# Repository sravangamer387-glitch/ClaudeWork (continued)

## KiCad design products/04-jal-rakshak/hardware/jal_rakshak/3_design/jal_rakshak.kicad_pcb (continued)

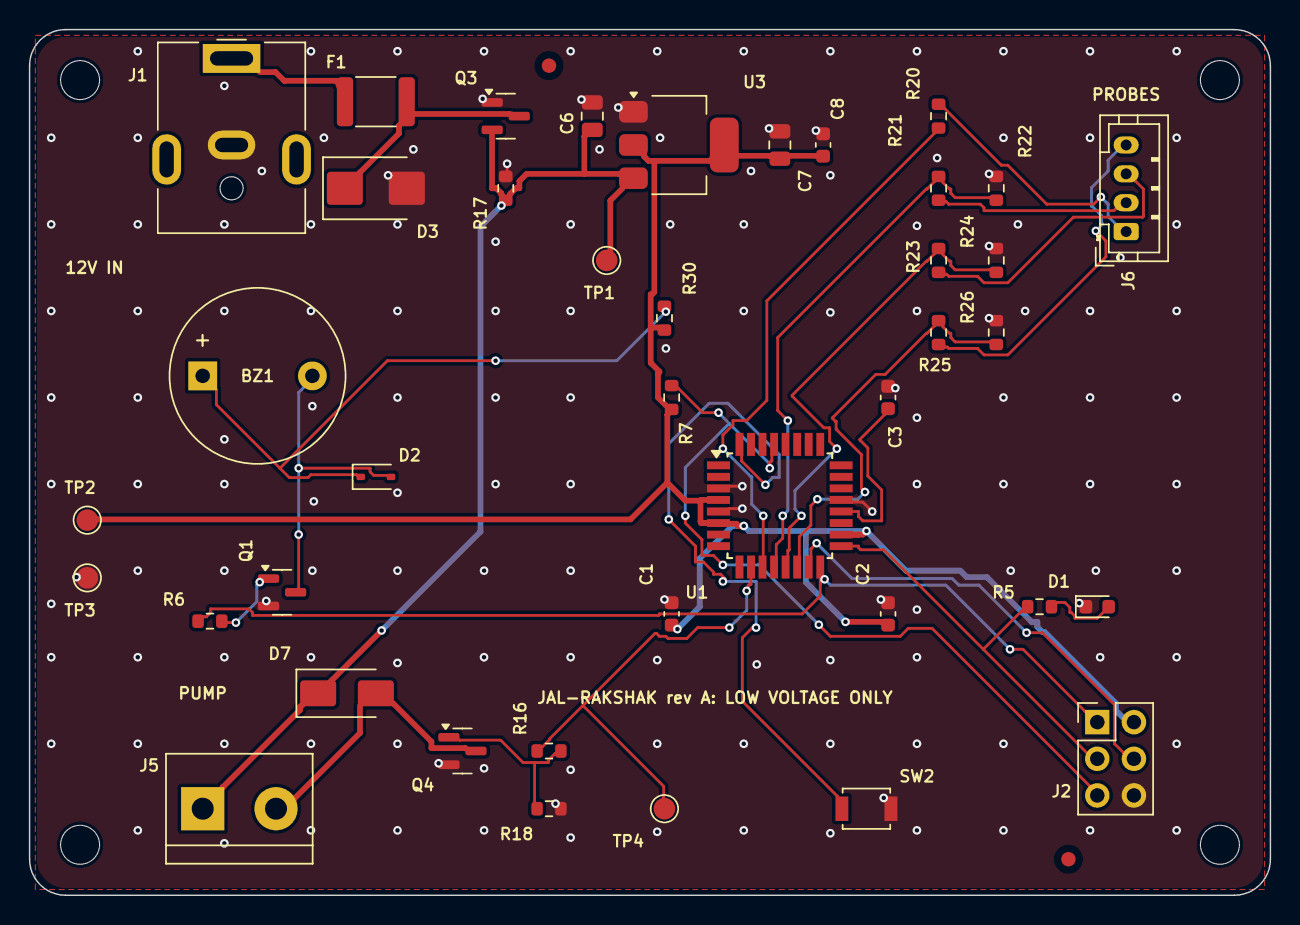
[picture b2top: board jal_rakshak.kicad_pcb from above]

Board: 2 copper layers, 86.0 x 60.0 mm, 46 parts (0 on the bottom side), 26 nets.

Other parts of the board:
FID1, FID2: Fiducial; Fiducial_1mm_Mask2mm
H1, H2, H3, H4: M2.5; MountingHole_2.7mm_M2.5

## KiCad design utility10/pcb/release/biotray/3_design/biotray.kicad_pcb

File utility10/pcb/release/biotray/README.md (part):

# BioTray vertical-farm tray controller (ESP32-S3, MQTT) (rev A)

BioTray vertical-farm tray controller (100 x 80 mm): ESP32-S3 (WiFi/MQTT), 12 V input with PTC, TVS and reverse-polarity PMOS, 5 V buck and 3.3 V LDO, four low-side 12 V outputs (2 pumps, fan, PWM grow light), DS18B20, I2C, water-level and analog pH/EC inputs.

**Status: engineering release, software-verified only (ERC on the netlist, KiCad DRC, netlist cross-check, SPICE where noted). Not yet built, not reviewed by a second engineer, not certified.**

## Specification
- Board 100 x 80 mm, 2 layers, 1.6 mm FR-4, 1 oz copper, rounded corners R2.5 mm, 3 x M2.5 mounting holes, 2 fiducials.
- Rules used: min track 0.2 mm (power 0.4 mm), min clearance 0.15 mm, via 0.6/0.3 mm, GND pour on both layers, 241 stitching vias.
- Finish: ENIG recommended (HASL lead-free acceptable); green mask, white silk; IPC class 2.
- 67 parts, 39 nets.

## Circuit description
- **Power:** 12 V barrel jack -> 1.1 A PTC -> SMBJ15A TVS -> AO3401A reverse-polarity PMOS with a 12 V zener gate clamp -> VM; AP63205 buck (4.7 uH, 2 x 22 uF) makes 5 V; AP2112K makes 3.3 V; USB VBUS joins 5 V through an SS14.
- **Outputs:** AO3400A low-side switches with 100 ohm gate resistors and 100 k pull-downs; SS14 flyback diodes on pumps and fan; the light output has none (LED strip).
- **Inputs:** DS18B20 (4.7 k pull-up), I2C 4-pin with 4.7 k pull-ups, float switch with 10 k pull-up, pH and EC through 1 k + 100 nF (module outputs must stay under 3 V).

## Power
About 0.15 A at 12 V idle (WiFi on); loads add to this and must stay under the 1.1 A PTC hold current.

## Verification
| Check | Result |
|---|---|
| Electrical rule check on the netlist (own ERC: unconnected pins, single-pin nets, output conflicts, unpowered supplies, symbol/footprint pin match) | 0 errors, 0 warnings |
| KiCad DRC | 0 errors, 0 warnings; unconnected pads: 0 |
| Schematic netlist equals PCB netlist | yes |
| Router failures | 0 |
| 3D STEP export | yes |
| Independent Gerber parse (gerbonara): layers parsed, outline size equals the design | 9 layers, outline [100.1, 80.1] mm, match |

Enclosure: printed mounting plate 116 x 96 mm for an IP65 box of at least 120 x 100 x 31 mm inside. wet environment: mount on this plate inside an IP65 ABS junction box with cable glands; keep the box above the water line; use a GFCI-protected 12 V adapter

## Bill of materials
| Ref | Value | Footprint | Manufacturer part | LCSC # | LCSC status |
|---|---|---|---|---|---|
| J2 | 12 V DC in | BarrelJack_CUI_PJ-063AH_Horizontal | CUI/Same Sky PJ-063AH | C22434582 | verified |
| F1 | PTC 1A 16V | Fuse_1812_4532Metric | Littelfuse 1812L110/16DR | C142746 | verified |
| D3 | SMBJ15A | D_SMB | Littelfuse SMBJ15A | C83846 | verified |
| Q5 | AO3401A | SOT-23 | AO3401A | C15127 | verified |
| D4 | BZT52C12 | D_SOD-123 | DIODES BZT52C12-7-F | C124196 | verified |
| R40 | 10k | R_0603_1608Metric | 0603 10k 1% | C25804 | verified |
| C30 | 100u/35V | CP_Elec_6.3x7.7 | Lelon VZH101M1VTR-0607 | C176683 | verified |
| C31 | 10u/50V | C_1210_3225Metric | Samsung CL32A106KBJNNNE | C380537 | verified |
| U2 | AP63205WU-7 | TSOT-23-6 | AP63205WU-7 | C2071056 | verified |
| R41 | 100k | R_0603_1608Metric | 0603 100k 1% | C25803 | verified |
| C32 | 100n | C_0603_1608Metric | Samsung CL10B104KB8NNNC 0603 100nF X7R 50V | C1591 | verified |
| L1 | 4.7u | L_Changjiang_FNR5040S | Changjiang FNR5040S4R7MT | C167963 | verified |
| C33 | 22u/10V | C_0805_2012Metric | Samsung CL21A226MPQNNNE | C29277 | verified |
| C34 | 22u/10V | C_0805_2012Metric | Samsung CL21A226MPQNNNE | C29277 | verified |
| D5 | SS14 | D_SMA | SS14 | C84343 | verified |
| U3 | AP2112K-3.3 | SOT-23-5 | AP2112K-3.3TRG1 | C51118 | verified |
| C35 | 1u | C_0603_1608Metric | 0603 1uF X7R | C15849 | verified |
| C36 | 10u | C_0805_2012Metric | 0805 10uF X5R | C15850 | verified |
| U1 | ESP32-S3-WROOM-1-N8 | ESP32-S3-WROOM-1 | ESP32-S3-WROOM-1-N8 | C2913198 | verified |
| C37 | 100n | C_0603_1608Metric | Samsung CL10B104KB8NNNC 0603 100nF X7R 50V | C1591 | verified |
| C38 | 10u | C_0805_2012Metric | 0805 10uF X5R | C15850 | verified |
| R42 | 10k | R_0603_1608Metric | 0603 10k 1% | C25804 | verified |
| C39 | 1u | C_0603_1608Metric | 0603 1uF X7R | C15849 | verified |
| SW2 | Reset (EN) | SW_SPST_B3U-1000P | Omron B3U-1000P | C231329 | verified |
| SW3 | Boot (IO0) | SW_SPST_B3U-1000P | Omron B3U-1000P | C231329 | verified |
| J1 | USB-C | USB_C_Receptacle_HRO_TYPE-C-31-M-12 | TYPE-C-31-M-12 | C165948 | verified |
| R43 | 5.1k | R_0603_1608Metric | 0603 5.1k 1% | C23186 | verified |
| R44 | 5.1k | R_0603_1608Metric | 0603 5.1k 1% | C23186 | verified |
| D6 | Green | LED_0603_1608Metric | Hubei KENTO KT-0603YG yellow-green 570 nm, Vf about 2 V (lights well from 3.3 V with 1 k; the Everlight 19-217 green was out of stock) | C2289 | verified |
| R45 | 1k | R_0603_1608Metric | 0603 1k 1% | C21190 | verified |
| J7 | Water temp DS18B20 | JST_PH_B3B-PH-K_1x03_P2.00mm_Vertical | JST B3B-PH-K-S(LF)(SN) | C131339 | verified |
| R46 | 4.7k | R_0603_1608Metric | 0603 4.7k 1% | C23162 | verified |
| J8 | I2C (BH1750 / SHT31) | JST_PH_B4B-PH-K_1x04_P2.00mm_Vertical | JST B4B-PH-K-S(LF)(SN) | C131334 | verified |
| R47 | 4.7k | R_0603_1608Metric | 0603 4.7k 1% | C23162 | verified |
| R48 | 4.7k | R_0603_1608Metric | 0603 4.7k 1% | C23162 | verified |
| J9 | Water-level float switch | JST_PH_B2B-PH-K_1x02_P2.00mm_Vertical | JST B2B-PH-K-S(LF)(SN) | C131337 | verified |
| R49 | 10k | R_0603_1608Metric | 0603 10k 1% | C25804 | verified |
| J10 | pH module (0-3 V analog) | JST_PH_B3B-PH-K_1x03_P2.00mm_Vertical | JST B3B-PH-K-S(LF)(SN) | C131339 | verified |
| R50 | 1k | R_0603_1608Metric | 0603 1k 1% | C21190 | verified |
| C40 | 100n | C_0603_1608Metric | Samsung CL10B104KB8NNNC 0603 100nF X7R 50V | C1591 | verified |
| J11 | EC module (0-3 V analog) | JST_PH_B3B-PH-K_1x03_P2.00mm_Vertical | JST B3B-PH-K-S(LF)(SN) | C131339 | verified |
| R51 | 1k | R_0603_1608Metric | 0603 1k 1% | C21190 | verified |
| C41 | 100n | C_0603_1608Metric | Samsung CL10B104KB8NNNC 0603 100nF X7R 50V | C1591 | verified |
| J12 | UART flash/debug (USB-serial adapter) | JST_PH_B3B-PH-K_1x03_P2.00mm_Vertical | JST B3B-PH-K-S(LF)(SN) | C131339 | verified |
| TP1 | TP | TestPoint_Pad_D1.5mm |  |  |  |
| TP2 | TP | TestPoint_Pad_D1.5mm |  |  |  |
| TP3 | TP | TestPoint_Pad_D1.5mm |  |  |  |
| TP4 | TP | TestPoint_Pad_D1.5mm |  |  |  |
| Q1 | AO3400A | SOT-23 | AO3400A | C20917 | verified |
| R10 | 100 | R_0603_1608Metric | UNI-ROYAL 0603WAF1000T5E | C22775 | verified |
| R14 | 100k | R_0603_1608Metric | 0603 100k 1% | C25803 | verified |
| J3 | Pump 1 | JST_PH_B2B-PH-K_1x02_P2.00mm_Vertical | JST B2B-PH-K-S(LF)(SN) | C131337 | verified |
| D10 | SS14 | D_SMA | SS14 | C84343 | verified |
| Q2 | AO3400A | SOT-23 | AO3400A | C20917 | verified |
| R11 | 100 | R_0603_1608Metric | UNI-ROYAL 0603WAF1000T5E | C22775 | verified |
| R15 | 100k | R_0603_1608Metric | 0603 100k 1% | C25803 | verified |
| J4 | Pump 2 | JST_PH_B2B-PH-K_1x02_P2.00mm_Vertical | JST B2B-PH-K-S(LF)(SN) | C131337 | verified |
| D11 | SS14 | D_SMA | SS14 | C84343 | verified |
| Q3 | AO3400A | SOT-23 | AO3400A | C20917 | verified |
| R12 | 100 | R_0603_1608Metric | UNI-ROYAL 0603WAF1000T5E | C22775 | verified |
| R16 | 100k | R_0603_1608Metric | 0603 100k 1% | C25803 | verified |
| J5 | Grow light (PWM) | JST_PH_B2B-PH-K_1x02_P2.00mm_Vertical | JST B2B-PH-K-S(LF)(SN) | C131337 | verified |
| Q4 | AO3400A | SOT-23 | AO3400A | C20917 | verified |
| R13 | 100 | R_0603_1608Metric | UNI-ROYAL 0603WAF1000T5E | C22775 | verified |
| R17 | 100k | R_0603_1608Metric | 0603 100k 1% | C25803 | verified |
| J6 | Fan | JST_PH_B2B-PH-K_1x02_P2.00mm_Vertical | JST B2B-PH-K-S(LF)(SN) | C131337 | verified |
| D13 | SS14 | D_SMA | SS14 | C84343 | verified |

`verified` = LCSC number confirmed by web search on 2026-10-31/11-01; `memory` = from my recollection, **check on lcsc.com before ordering**; empty = no number chosen (through-hole connectors, switches, buzzer, test points: hand-assembled or chosen by the buyer). `*_JLC_BOM.csv` / `*_JLC_CPL.csv` list only the parts with an LCSC number; JLCPCB rotation corrections (CPL) must be checked in their viewer.

## Assembly notes
- Reflow (JLCPCB SMT): all SMD parts with an LCSC number. Hand-solder: JST connectors, pin headers, buzzer, switches, test points as listed in the BOM. Fiducials and mounting holes are in the Gerbers.
- Polarity: LED cathode toward GND (silk marks), electrolytic none, diode D2 cathode to +V, Q2 orientation as footprint (SOT-23 pin 1 = gate).
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
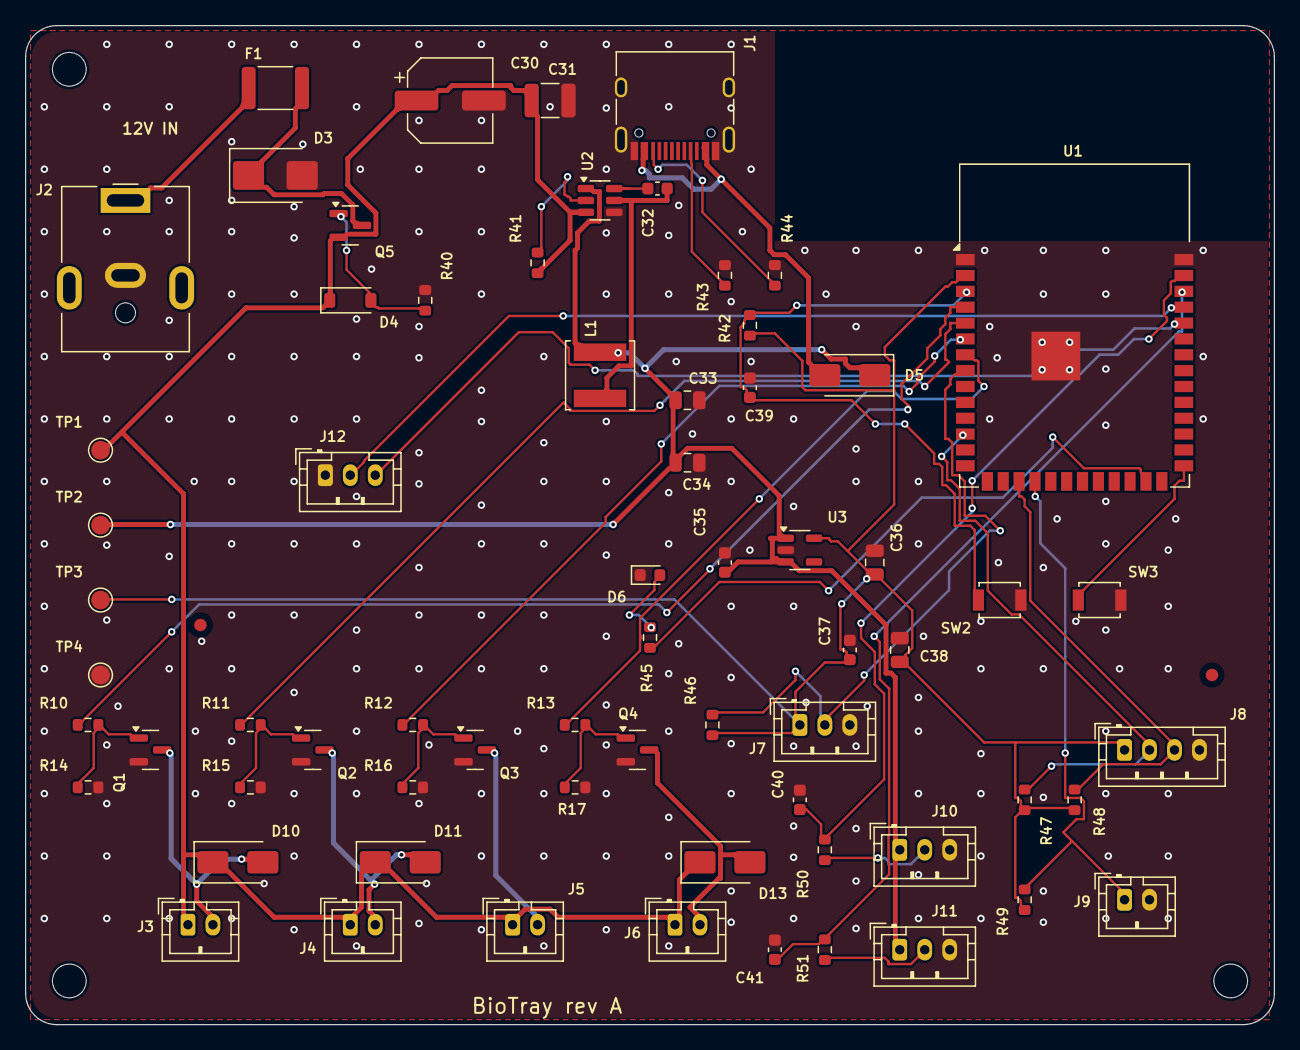
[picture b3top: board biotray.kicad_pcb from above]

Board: 2 copper layers, 100.0 x 80.0 mm, 72 parts (0 on the bottom side), 39 nets.

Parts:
C30: 100u/35V; CP_Elec_6.3x7.7
C31: 10u/50V; C_1210_3225Metric
C32, C37, C40, C41: 100n; C_0603_1608Metric
C33, C34: 22u/10V; C_0805_2012Metric
C35, C39: 1u; C_0603_1608Metric
C36, C38: 10u; C_0805_2012Metric
D3: SMBJ15A; D_SMB
D4: BZT52C12; D_SOD-123
D5, D10, D11, D13: SS14; D_SMA
D6: Green; LED_0603_1608Metric
F1: PTC 1A 16V; Fuse_1812_4532Metric
FID1, FID2: Fiducial; Fiducial_1mm_Mask2mm
H1, H2, H3: M2.5; MountingHole_2.7mm_M2.5
J1: USB-C; USB_C_Receptacle_HRO_TYPE-C-31-M-12
J2: 12 V DC in; BarrelJack_CUI_PJ-063AH_Horizontal
J3: Pump 1; JST_PH_B2B-PH-K_1x02_P2.00mm_Vertical
J4: Pump 2; JST_PH_B2B-PH-K_1x02_P2.00mm_Vertical
J5: Grow light (PWM); JST_PH_B2B-PH-K_1x02_P2.00mm_Vertical
J6: Fan; JST_PH_B2B-PH-K_1x02_P2.00mm_Vertical
J7: Water temp DS18B20; JST_PH_B3B-PH-K_1x03_P2.00mm_Vertical
J8: I2C (BH1750 / SHT31); JST_PH_B4B-PH-K_1x04_P2.00mm_Vertical
J9: Water-level float switch; JST_PH_B2B-PH-K_1x02_P2.00mm_Vertical
J10: pH module (0-3 V analog); JST_PH_B3B-PH-K_1x03_P2.00mm_Vertical
J11: EC module (0-3 V analog); JST_PH_B3B-PH-K_1x03_P2.00mm_Vertical
J12: UART flash/debug (USB-serial adapter); JST_PH_B3B-PH-K_1x03_P2.00mm_Vertical
L1: 4.7u; L_Changjiang_FNR5040S
Q1, Q2, Q3, Q4: AO3400A; SOT-23
Q5: AO3401A; SOT-23
R10, R11, R12, R13: 100; R_0603_1608Metric
R14, R15, R16, R17, R41: 100k; R_0603_1608Metric
R40, R42, R49: 10k; R_0603_1608Metric
R43, R44: 5.1k; R_0603_1608Metric
R45, R50, R51: 1k; R_0603_1608Metric
R46, R47, R48: 4.7k; R_0603_1608Metric
SW2: Reset (EN); SW_SPST_B3U-1000P
SW3: Boot (IO0); SW_SPST_B3U-1000P
TP1, TP2, TP3, TP4: TP; TestPoint_Pad_D1.5mm
U1: ESP32-S3-WROOM-1-N8; ESP32-S3-WROOM-1
U2: AP63205WU-7; TSOT-23-6
U3: AP2112K-3.3; SOT-23-5

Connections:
+3V3: C36.1, C37.1, C38.1, J7.1, J8.1, R42.1, R46.1, R47.1, R48.1, R49.1, TP3.1, U1.2, U3.5
+5V: C33.1, C34.1, C35.1, D5.1, J10.1, J11.1, L1.2, TP2.1, U2.1, U3.1, U3.3
BOOT: SW3.1, U1.27
BST: C32.1, U2.6
CC1: J1.A5, R43.1
CC2: J1.B5, R44.1
EC_ADC: C41.1, R51.2, U1.38
EC_J: J11.2, R51.1
EN: C39.1, R42.2, SW2.1, U1.3
EN_B: R41.2, U2.2
FAN_D: D13.2, J6.2, Q4.3
FAN_G: R13.1, U1.7
FAN_GR: Q4.1, R13.2, R17.1
GATE: D4.2, Q5.1, R40.1
GND: C30.2, C31.2, C33.2, C34.2, C35.2, C36.2, C37.2, C38.2, C39.2, C40.2, C41.2, D3.2, D6.1, J1.A1, J1.A12, J1.B1, J1.B12, J1.S1, J2.2, J7.3, J8.4, J9.2, J10.3, J11.3, J12.1, Q1.2, Q2.2, Q3.2, Q4.2, R14.2, R15.2, R16.2, R17.2, R40.2, R43.2, R44.2, SW2.2, SW3.2, TP4.1, U1.1, U1.40, U1.41, U2.4, U3.2
LED: R45.1, U1.25
LED_A: D6.2, R45.2
LEVEL: J9.1, R49.2, U1.18
LIGHT_D: J5.2, Q3.3
LIGHT_G: R12.1, U1.6
LIGHT_GR: Q3.1, R12.2, R16.1
ONEWIRE: J7.2, R46.2, U1.8
PH_ADC: C40.1, R50.2, U1.39
PH_J: J10.2, R50.1
PUMP1_D: D10.2, J3.2, Q1.3
PUMP1_G: R10.1, U1.4
PUMP1_GR: Q1.1, R10.2, R14.1
PUMP2_D: D11.2, J4.2, Q2.3
PUMP2_G: R11.1, U1.5
PUMP2_GR: Q2.1, R11.2, R15.1
SCL: J8.3, R48.2, U1.17
SDA: J8.2, R47.2, U1.12
SW: C32.2, L1.1, U2.5
UART_RX: J12.3, U1.36
UART_TX: J12.2, U1.37
VBUS: D5.2, J1.A4, J1.A9, J1.B4, J1.B9
VIN12: F1.1, J2.1
VIN_F: D3.1, F1.2, Q5.3
VM: C30.1, C31.1, D4.1, D10.1, D11.1, D13.1, J3.1, J4.1, J5.1, J6.1, Q5.2, R41.1, TP1.1, U2.3

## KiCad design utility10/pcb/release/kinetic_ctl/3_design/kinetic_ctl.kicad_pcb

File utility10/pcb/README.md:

# PCB designs - rev B (engineering release)

Utility tools: **Seeti Counter**, **Bijli Meter Reader** (USB-C), **Rain Alert Bell** (+ rain plate), **Fridge Door Guard**, **Chulha Timers**, **Tap Litre Meter**, **Bijli Log** (USB-C + backup battery), **Gas Taraju** (HX711 load-cell scale). Other products: **Desi Arcade** (toy, 3 games) and **Kheti-Mitra** (12 V irrigation controller). The Jal-Netra ultrasonic meter board is in `../../jal-netra/hardware/`. The two laser-cut tools (Masala Rack, Laptop Stand) have no PCB. Not done: Prayog STEM kit board (12 plug-in modules), Beat Runner (16-LED strip), and the parked mains products (Jal-Rakshak) and stopped gas alarm.

**Status: software-verified engineering release. Nothing here has been built, reviewed by a second engineer, or sent to a fab. Before ordering, an electronics engineer must complete `REVIEW_CHECKLIST.md`.** Order 5 prototypes first. Boards added later (Tier B tools, Desi Arcade, Kheti-Mitra) reuse the verified blocks of the first four and had less iteration.

## What rev B adds over the first draft
Reverse-battery protection (P-MOSFET), TVS surge protection on the USB-C VBUS line and on the rain-plate cable, PTC fuse, correct USB-C sink resistors (HRO Type-C receptacle, 5.1 k on CC1/CC2), test points, four M2.5 mounting holes and two fiducials per board, rounded corners, ground pours on both layers with stitching vias, power traces 0.4 mm, JLCPCB-format BOM/CPL with LCSC numbers (the ones I could verify are marked), a 3D STEP model, fabrication-notes PDF, assembly drawing PDF, a parametric enclosure shell generated from the finished board with a collision check, SPICE simulations of the analog stages, and a readable schematic with real wires where it was safe to draw them. Two **design errors were found by simulation and fixed**: the microphone amplifier's feedback return into a weakly bypassed bias node had destroyed the low-frequency gain (fixed with a 10 uF bypass), and its first gain/bandwidth claim (101x, 9 kHz) did not match the final component values (34x, 26 kHz, so an anti-alias filter was added).

## Verification summary (all software)
| Board | Parts / nets | Own ERC errors | KiCad DRC errors | Unconnected | Schematic netlist = PCB netlist | Router failures |
|---|---|---|---|---|---|---|
| seeti_counter | 36 / 24 | 0 | 0 (0 warnings) | 0 | yes | 0 |
| bijli_meter_reader | 23 / 17 | 0 | 0 (0 warnings) | 0 | yes | 0 |
| rain_alert_main | 27 / 19 | 0 | 0 (0 warnings) | 0 | yes | 0 |
| rain_plate | 1 / 2 | 0 | 0 (0 warnings) | 0 | yes | 0 |
| fridge_door_guard | 24 / 17 | 0 | 0 (0 warnings) | 0 | yes | 0 |
| chulha_timers | 22 / 18 | 0 | 0 (0 warnings) | 0 | yes | 0 |
| tap_litre_meter | 28 / 19 | 0 | 0 (0 warnings) | 0 | yes | 0 |
| bijli_log | 31 / 19 | 0 | 0 (0 warnings) | 0 | yes | 0 |
| gas_taraju | 35 / 28 | 0 | 0 (0 warnings) | 0 | yes | 0 |
| desi_arcade | 27 / 25 | 0 | 0 (0 warnings) | 0 | yes | 0 |
| kheti_mitra | 37 / 22 | 0 | 0 (0 warnings) | 0 | yes | 0 |
| jal_netra | 78 / 51 | 0 | 0 (0 warnings) | 0 | yes | 0 |
| prayog_hub | 34 / 32 | 0 | 0 (0 warnings) | 0 | yes | 0 |
| beat_runner | 53 / 46 | 0 | 0 (0 warnings) | 0 | yes | 0 |

How it was checked: (1) own ERC on the netlist (unconnected pins, single-pin nets, output conflicts, unpowered supply nets, symbol-to-footprint pin match; KiCad 7's command line has no ERC); (2) KiCad 7 DRC through its Python API (clearance, hole spacing, courtyards, mask bridges, silkscreen); (3) schematic export compared pin-group by pin-group with the PCB netlist (this caught an accidental short that my own auto-wiring had drawn between CC2 and VBUS); (4) independent Gerber parse with a second library (gerbonara): layers read, outline size equals the design; (5) SPICE (ngspice) for the Seeti amplifier and rain-plate sense; arithmetic model for the Bijli sensor head. The rain plate's mask-bridge errors are waived on purpose (one mask opening spans both gold electrodes).

## Folder map
| Path | Contents |
|---|---|
| `release/<board>/` | everything to review or order: KiCad 7 project, Gerber zip, JLC BOM/CPL, full BOM with LCSC status, STEP, schematic PDF, assembly and copper PDFs, fab-notes PDF, enclosure STLs, board images, board README (design notes, simulations, bring-up) |
| `boards/*.py` | design source: parts, positions, nets, schematic layout, enclosure cut-outs |
| `build.py` `route.py` `sch2.py` `erc.py` `placecheck.py` `retouch.py` | toolchain: schematic writer, 0.05 mm-grid two-layer router, placement check, silkscreen touch-up |
| `outputs.py` `package.py` `docgen.py` `fabdoc.py` `enclosure.py` `gerbercheck.py` | verification and manufacturing outputs |
| `sim/` | SPICE decks and results |
| `REVIEW_CHECKLIST.md` | engineer sign-off list |

Rebuild one board: `python3 build.py seeti` (3-8 minutes for the largest), then `python3 package.py seeti` (system Python with KiCad 7 `pcbnew`; the PNG/PDF/STL steps use a venv with cairosvg, matplotlib, trimesh, gerbonara).

## Honest limits
1. **Routing and placement are software-generated** (my own router; Freerouting could not be used here). The result passes every rule check, but a person should look at the analog routing, ground return paths and connector mechanics.
2. **Schematics are structured and partly wired, but not hand-drawn quality**; the engineer should tidy them for presentation.
3. **Parts:** LCSC numbers marked `verified` were found by web search (ATmega328P-AU C14877, MCP6001T-I/OT C116490, MMBT3904 C20526, 1N4148WS C2128, AO3401A C15127, TYPE-C-31-M-12 C165948); passive numbers are from memory and **must be checked**; connectors, switches, buzzer and TVS/PTC parts have no number yet. No price or stock was checked.
4. **Clock/voltage:** the 2 x AAA board must run at 4 MHz (8 MHz needs 2.7 V); the board README gives fuse values; confirm against the current ATmega328P datasheet.
5. **Not verified:** real sensor behaviour (microphone capsule, meter LED coupling, plate resistance in real rain), EMC/ESD tests, battery life (estimates only), thermal, mechanical fit of the enclosure with real parts (the STEP uses KiCad's stock 3D models).
6. Seeti's anti-alias filter is first-order only (about 8 dB at 16 kHz); production firmware should use timer-triggered ADC sampling at 16 kS/s.

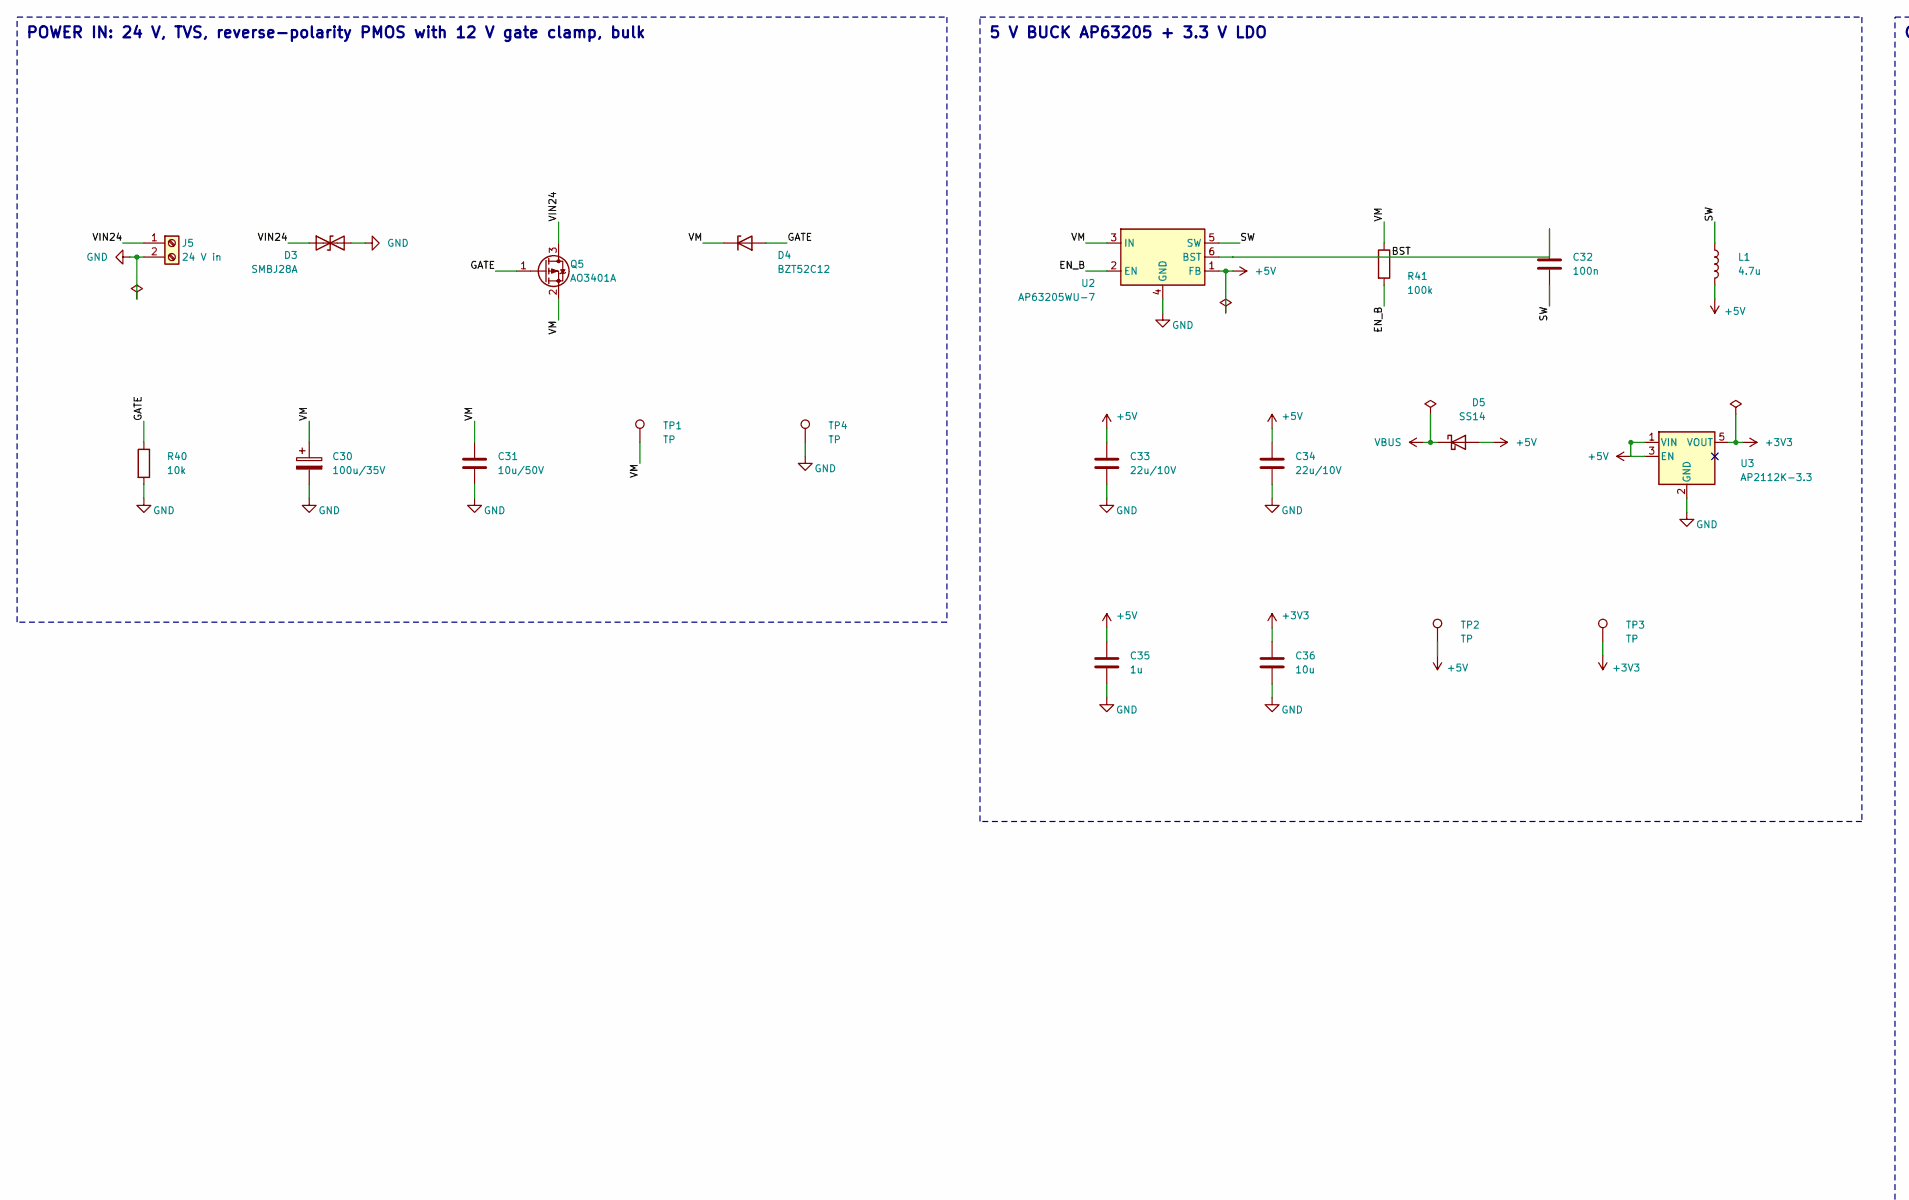
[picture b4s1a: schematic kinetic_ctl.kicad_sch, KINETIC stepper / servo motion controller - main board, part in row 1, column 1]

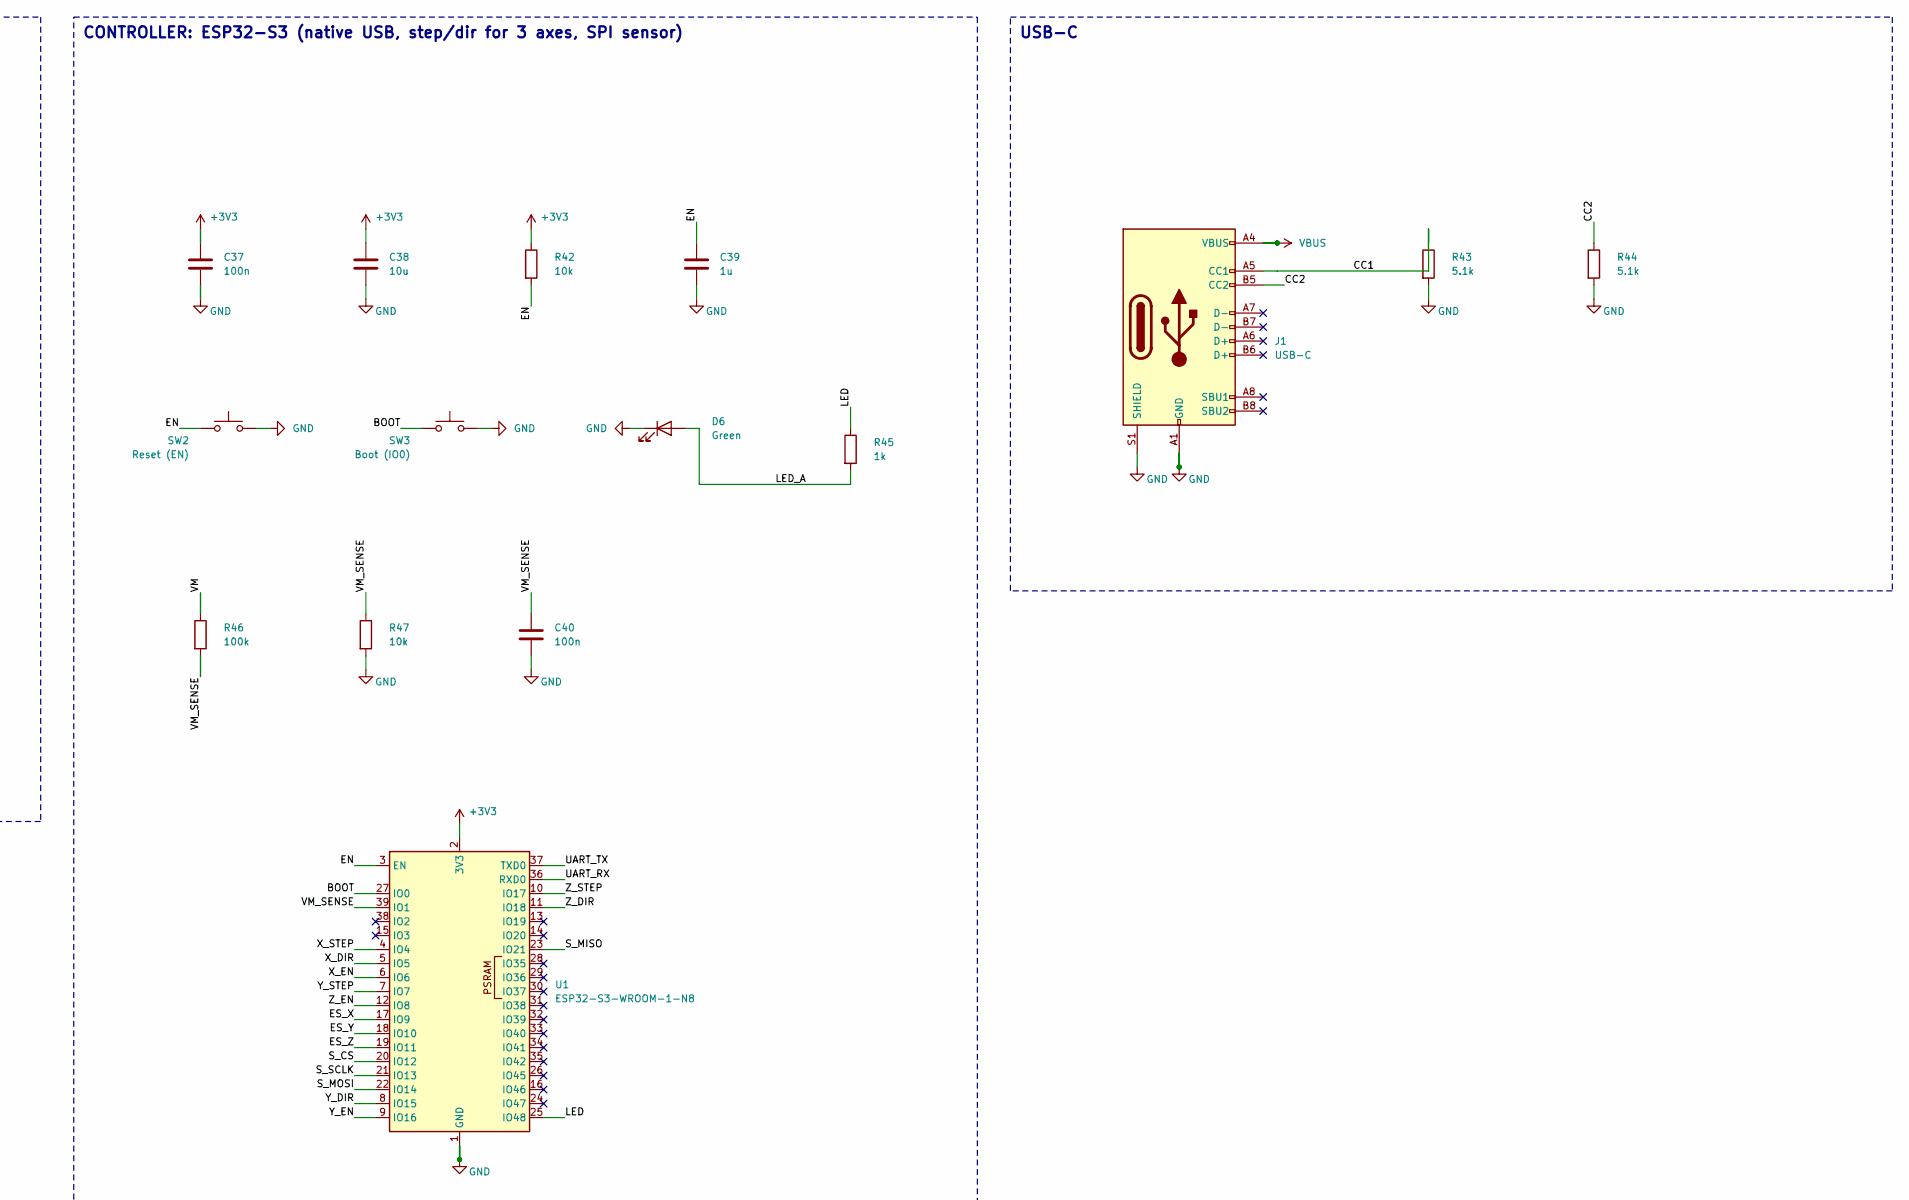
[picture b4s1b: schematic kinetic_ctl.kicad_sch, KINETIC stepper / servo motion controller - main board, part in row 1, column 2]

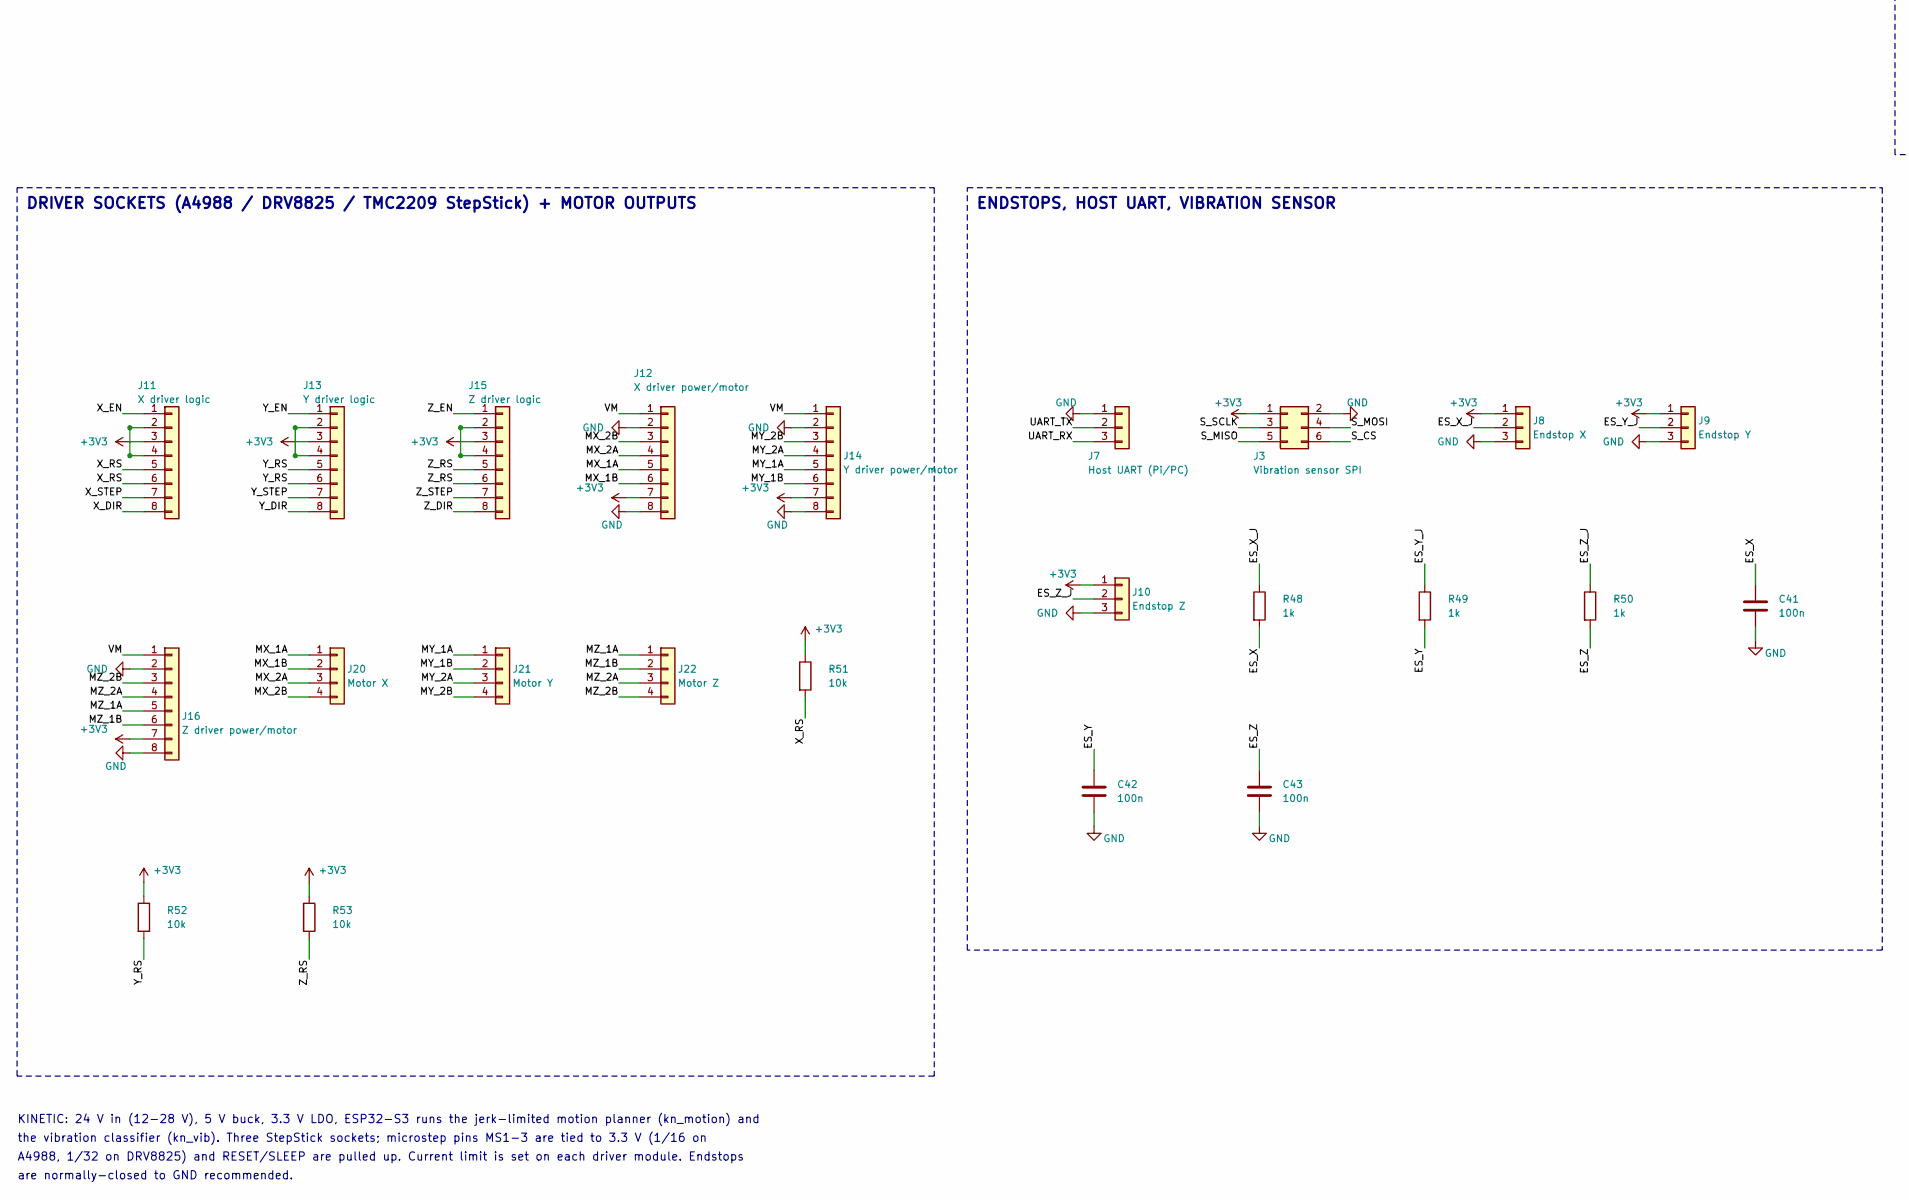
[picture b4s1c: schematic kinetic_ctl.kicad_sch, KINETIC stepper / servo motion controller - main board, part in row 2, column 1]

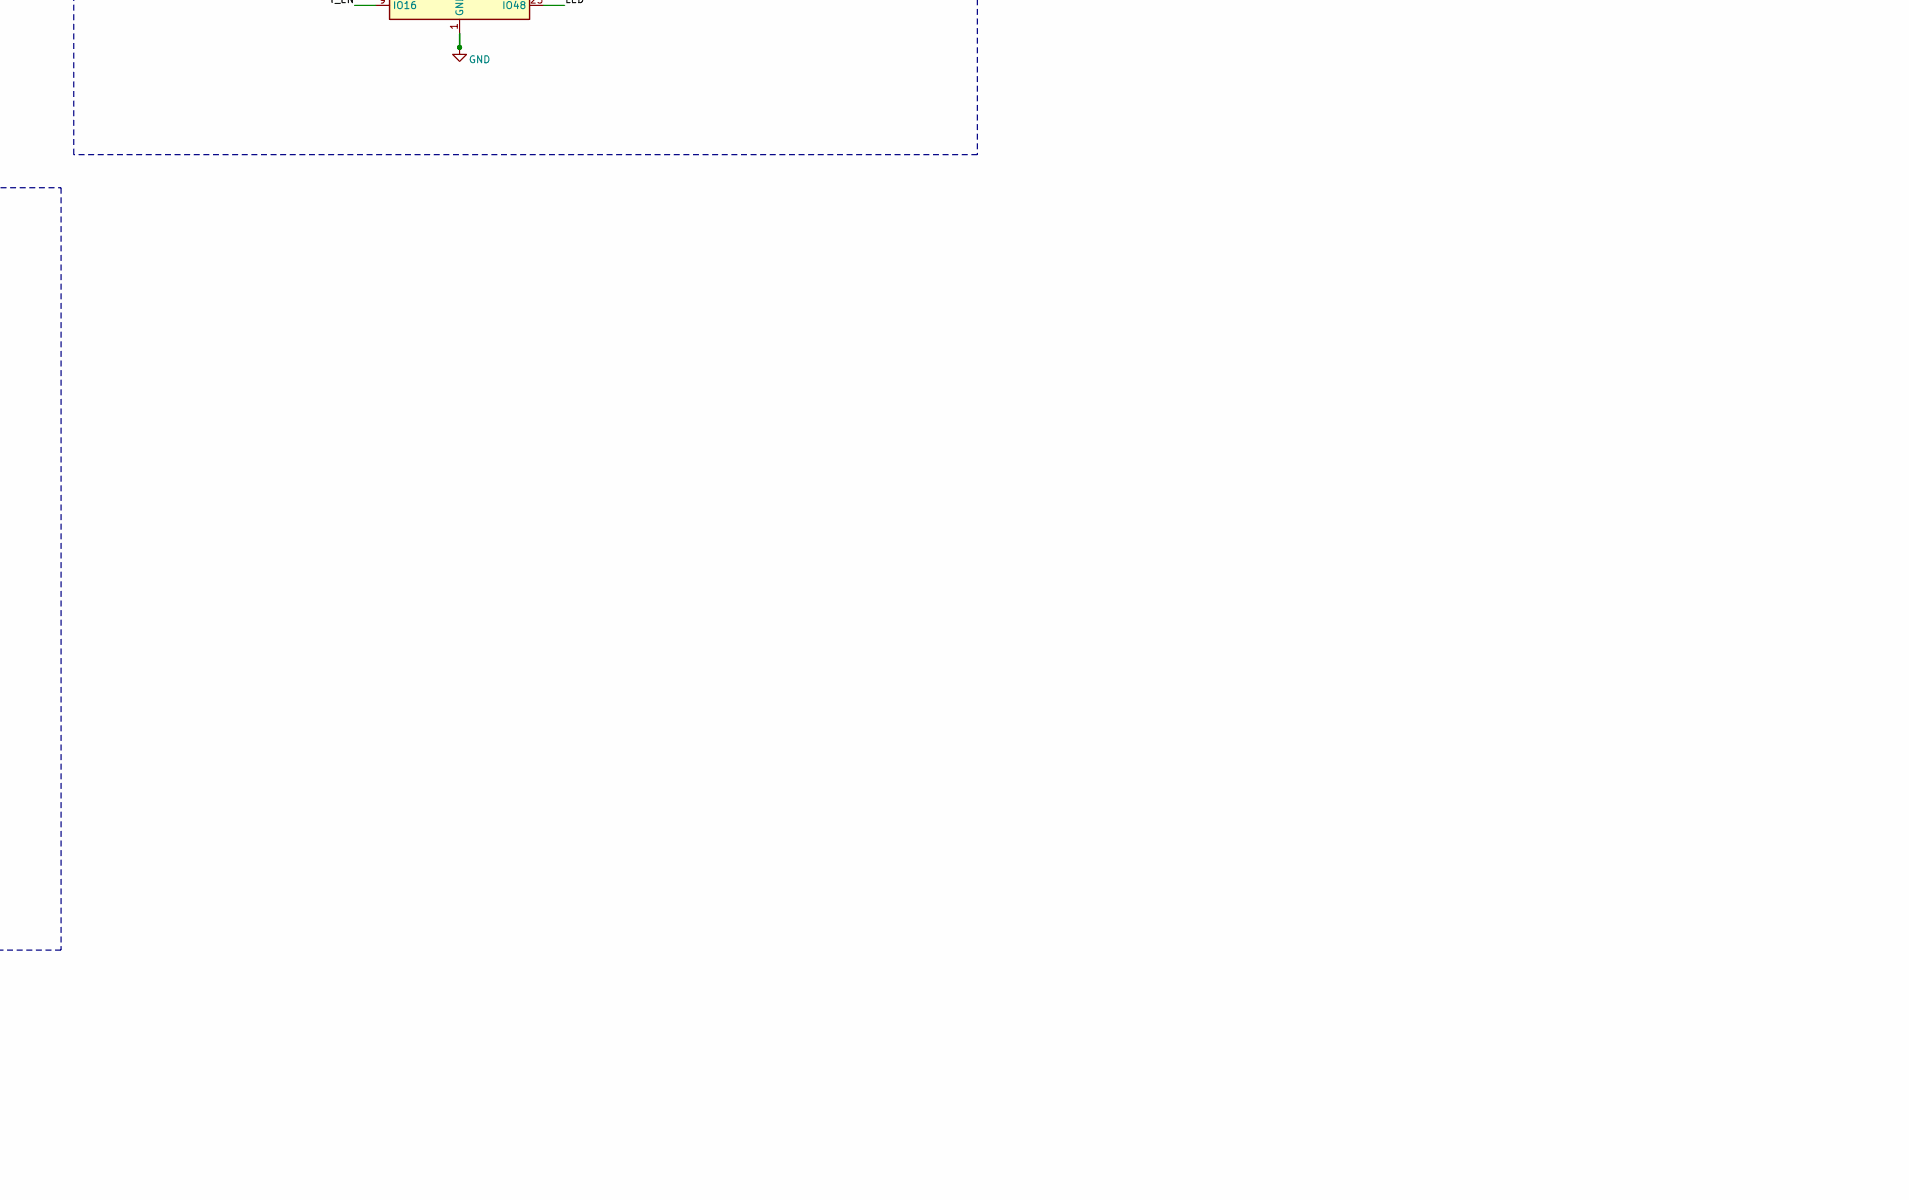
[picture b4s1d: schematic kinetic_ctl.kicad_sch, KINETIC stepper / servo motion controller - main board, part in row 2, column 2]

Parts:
C30: 100u/35V; CP_Elec_6.3x7.7
C31: 10u/50V; C_1210_3225Metric
C32, C37, C40, C41, C42, C43: 100n; C_0603_1608Metric
C33, C34: 22u/10V; C_0805_2012Metric
C35, C39: 1u; C_0603_1608Metric
C36, C38: 10u; C_0805_2012Metric
D3: SMBJ28A; D_SMB
D4: BZT52C12; D_SOD-123
D5: SS14; D_SMA
D6: Green; LED_0603_1608Metric
J1: USB-C; USB_C_Receptacle_HRO_TYPE-C-31-M-12
J3: Vibration sensor SPI; PinHeader_2x03_P2.54mm_Vertical
J5: 24 V in; TerminalBlock_bornier-2_P5.08mm
J7: Host UART (Pi/PC); JST_PH_B3B-PH-K_1x03_P2.00mm_Vertical
J8: Endstop X; JST_PH_B3B-PH-K_1x03_P2.00mm_Vertical
J9: Endstop Y; JST_PH_B3B-PH-K_1x03_P2.00mm_Vertical
J10: Endstop Z; JST_PH_B3B-PH-K_1x03_P2.00mm_Vertical
J11: X driver logic; PinSocket_1x08_P2.54mm_Vertical
J12: X driver power/motor; PinSocket_1x08_P2.54mm_Vertical
J13: Y driver logic; PinSocket_1x08_P2.54mm_Vertical
J14: Y driver power/motor; PinSocket_1x08_P2.54mm_Vertical
J15: Z driver logic; PinSocket_1x08_P2.54mm_Vertical
J16: Z driver power/motor; PinSocket_1x08_P2.54mm_Vertical
J20: Motor X; JST_PH_B4B-PH-K_1x04_P2.00mm_Vertical
J21: Motor Y; JST_PH_B4B-PH-K_1x04_P2.00mm_Vertical
J22: Motor Z; JST_PH_B4B-PH-K_1x04_P2.00mm_Vertical
L1: 4.7u; L_Changjiang_FNR5040S
Q5: AO3401A; SOT-23
R40, R42, R47, R51, R52, R53: 10k; R_0603_1608Metric
R41, R46: 100k; R_0603_1608Metric
R43, R44: 5.1k; R_0603_1608Metric
R45, R48, R49, R50: 1k; R_0603_1608Metric
SW2: Reset (EN); SW_SPST_B3U-1000P
SW3: Boot (IO0); SW_SPST_B3U-1000P
TP1, TP2, TP3, TP4: TP; TestPoint_Pad_D1.5mm
U1: ESP32-S3-WROOM-1-N8; ESP32-S3-WROOM-1
U2: AP63205WU-7; TSOT-23-6
U3: AP2112K-3.3; SOT-23-5

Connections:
+3V3: C36.1, C37.1, C38.1, J3.1, J8.1, J9.1, J10.1, J11.2, J11.3, J11.4, J12.7, J13.2, J13.3, J13.4, J14.7, J15.2, J15.3, J15.4, J16.7, R42.1, R51.1, R52.1, R53.1, TP3.1, U1.2 (3V3), U3.5 (VOUT)
BOOT: SW3.1, U1.27 (IO0)
BST: C32.1, U2.6 (BST)
CC1: J1.A5 (CC1), R43.1
CC2: J1.B5 (CC2), R44.1
EN: C39.1, R42.2, SW2.1, U1.3 (EN)
EN_B: R41.2, U2.2 (EN)
ES_X: C41.1, R48.2, U1.17 (IO9)
ES_X_J: J8.2, R48.1
ES_Y: C42.1, R49.2, U1.18 (IO10)
ES_Y_J: J9.2, R49.1
ES_Z: C43.1, R50.2, U1.19 (IO11)
ES_Z_J: J10.2, R50.1
GATE: D4.2 (A), Q5.1 (G), R40.1
GND: C30.2, C31.2, C33.2, C34.2, C35.2, C36.2, C37.2, C38.2, C39.2, C40.2, C41.2, C42.2, C43.2, D3.2 (A2), D6.1 (K), J1.A1 (GND), J1.A12 (GND), J1.B1 (GND), J1.B12 (GND), J1.S1 (SHIELD), J3.2, J5.2, J7.1, J8.3, J9.3, J10.3, J12.2, J12.8, J14.2, J14.8, J16.2, J16.8, R40.2, R43.2, R44.2, R47.2, SW2.2, SW3.2, TP4.1, U1.1 (GND), U1.40 (GND), U1.41 (GND), U2.4 (GND), U3.2 (GND)
LED: R45.1, U1.25 (IO48)
LED_A: D6.2 (A), R45.2
MX_1A: J12.5, J20.1
MX_1B: J12.6, J20.2
MX_2A: J12.4, J20.3
MX_2B: J12.3, J20.4
MY_1A: J14.5, J21.1
MY_1B: J14.6, J21.2
MY_2A: J14.4, J21.3
MY_2B: J14.3, J21.4
MZ_1A: J16.5, J22.1
MZ_1B: J16.6, J22.2
MZ_2A: J16.4, J22.3
MZ_2B: J16.3, J22.4
SW: C32.2, L1.1, U2.5 (SW)
S_CS: J3.6, U1.20 (IO12)
S_MISO: J3.5, U1.23 (IO21)
S_MOSI: J3.4, U1.22 (IO14)
S_SCLK: J3.3, U1.21 (IO13)
UART_RX: J7.3, U1.36 (RXD0)
UART_TX: J7.2, U1.37 (TXD0)
VIN24: D3.1 (A1), J5.1, Q5.3 (D)
VM: C30.1, C31.1, D4.1 (K), J12.1, J14.1, J16.1, Q5.2 (S), R41.1, R46.1, TP1.1, U2.3 (IN)
VM_SENSE: C40.1, R46.2, R47.1, U1.39 (IO1)
X_DIR: J11.8, U1.5 (IO5)
X_EN: J11.1, U1.6 (IO6)
X_RS: J11.5, J11.6, R51.2
X_STEP: J11.7, U1.4 (IO4)
Y_DIR: J13.8, U1.8 (IO15)
Y_EN: J13.1, U1.9 (IO16)
Y_RS: J13.5, J13.6, R52.2
Y_STEP: J13.7, U1.7 (IO7)
Z_DIR: J15.8, U1.11 (IO18)
Z_EN: J15.1, U1.12 (IO8)
Z_RS: J15.5, J15.6, R53.2
Z_STEP: J15.7, U1.10 (IO17)

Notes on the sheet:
POWER IN: 24 V, TVS, reverse-polarity PMOS with 12 V gate clamp, bulk
5 V BUCK AP63205 + 3.3 V LDO
CONTROLLER: ESP32-S3 (native USB, step/dir for 3 axes, SPI sensor)
USB-C
DRIVER SOCKETS (A4988 / DRV8825 / TMC2209 StepStick) + MOTOR OUTPUTS
ENDSTOPS, HOST UART, VIBRATION SENSOR
KINETIC: 24 V in (12-28 V), 5 V buck, 3.3 V LDO, ESP32-S3 runs the jerk-limited motion planner (kn_motion) and
the vibration classifier (kn_vib). Three StepStick sockets; microstep pins MS1-3 are tied to 3.3 V (1/16 on
A4988, 1/32 on DRV8825) and RESET/SLEEP are pulled up. Current limit is set on each driver module. Endstops
are normally-closed to GND recommended.

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
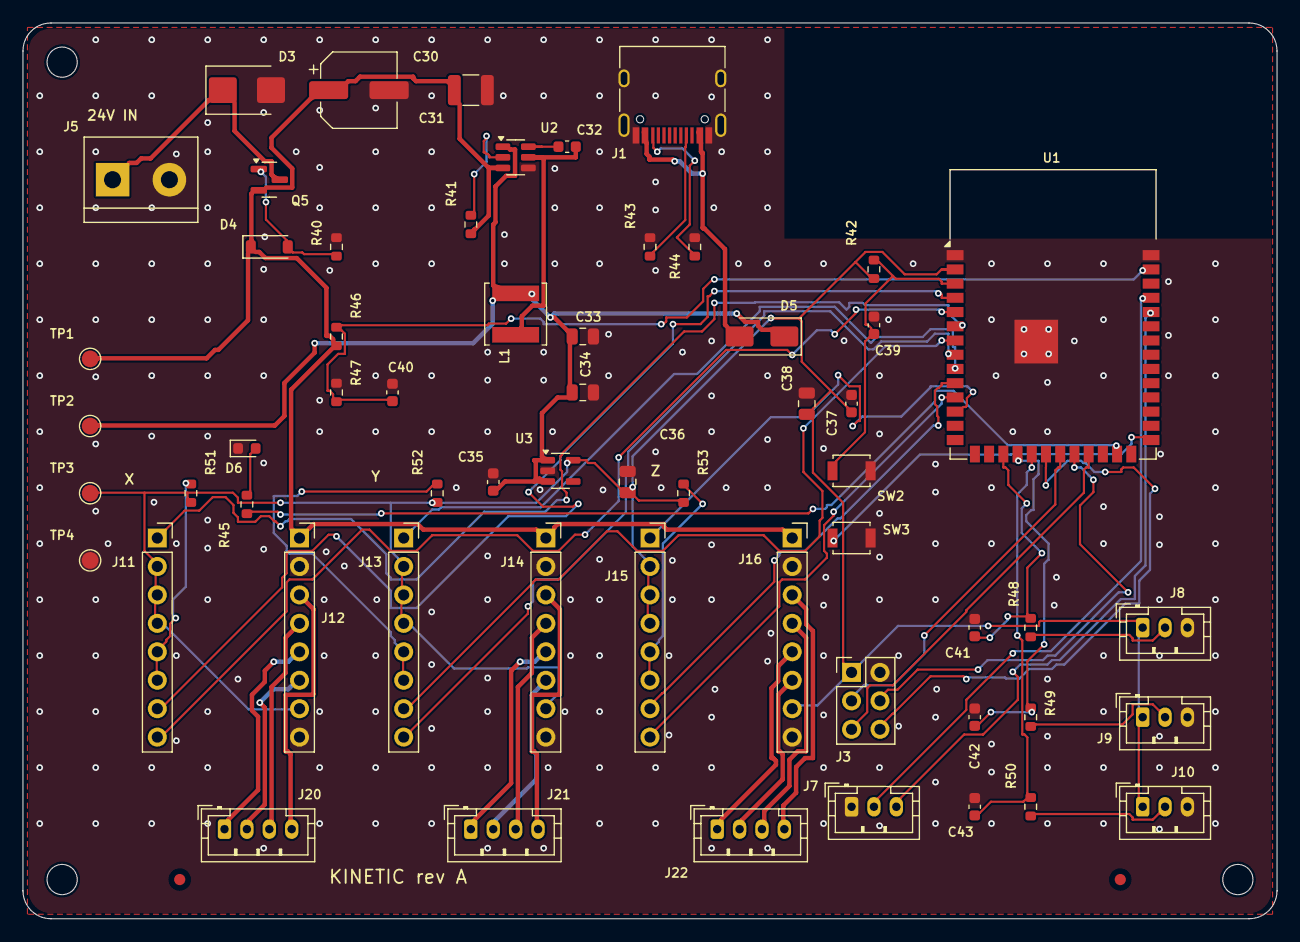
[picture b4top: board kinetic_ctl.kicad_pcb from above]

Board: 2 copper layers, 112.0 x 80.0 mm, 64 parts (0 on the bottom side), 53 nets.

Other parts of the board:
FID1, FID2: Fiducial; Fiducial_1mm_Mask2mm
H1, H2, H3: M2.5; MountingHole_2.7mm_M2.5
